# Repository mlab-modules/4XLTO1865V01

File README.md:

# 4XLTO1865V01 - LTO cells holder 

LTO cell holder for [SOLARMINIBAT01](https://github.com/mlab-modules/SOLARMINIBAT01) module.

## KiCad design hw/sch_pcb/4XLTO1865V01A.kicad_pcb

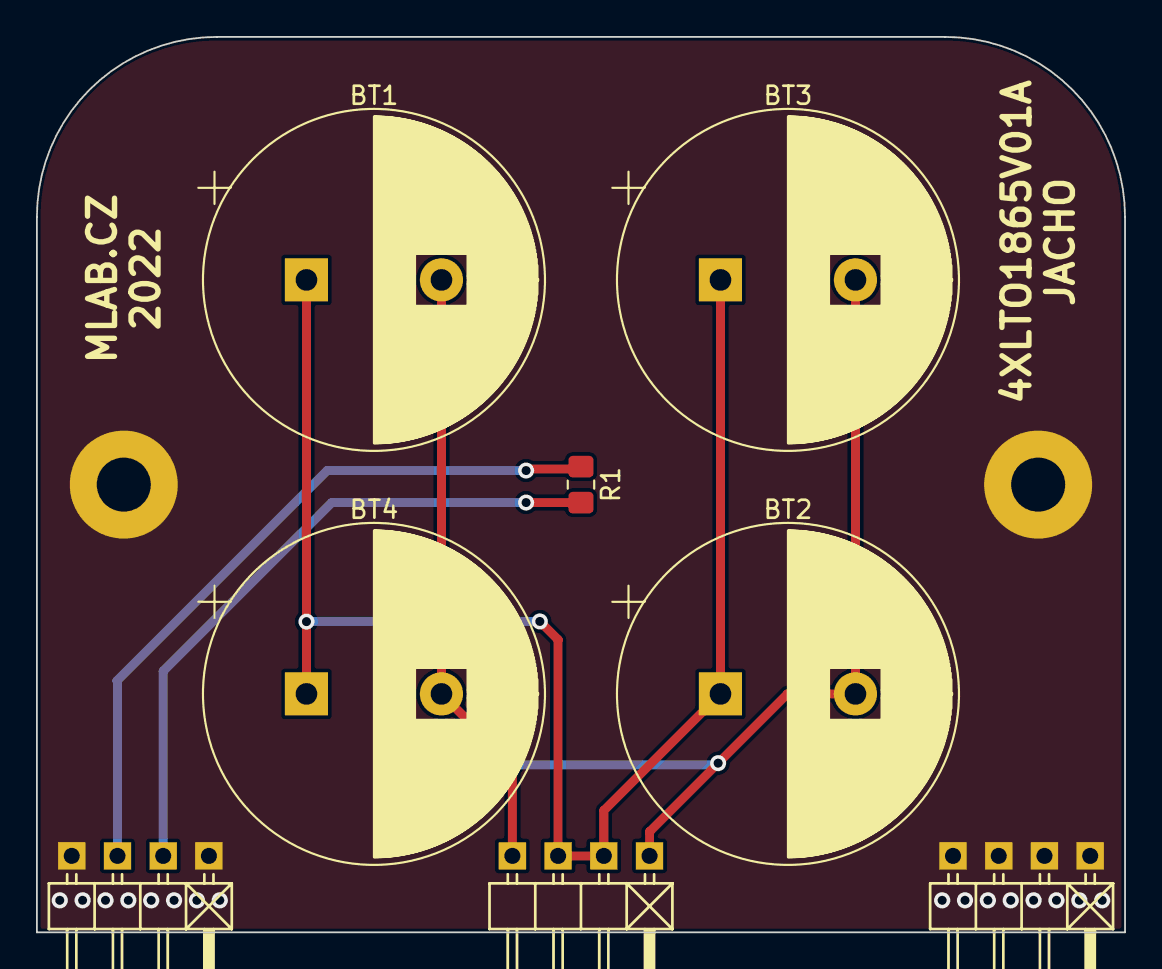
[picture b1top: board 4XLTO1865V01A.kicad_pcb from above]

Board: 2 copper layers, 60.5 x 49.7 mm, 10 parts (0 on the bottom side), 5 nets.

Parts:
BT1, BT2, BT3, BT4: LTO1865-13; LTO1865-13_D19.0mm_P7.50mm
J1, J2, J3: HEADER_2x04_PARALLEL; Angled_1x04
M1, M2: HOLE; MountingHole_3mm
R1: 10K NTC; R_0805_2012Metric_Pad1.20x1.40mm_HandSolder

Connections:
/Battery+: BT1.1 (+), BT2.1 (+), BT3.1 (+), BT4.1 (+), J1.2, J1.3
/Battery-: BT1.2 (-), BT2.2 (-), BT3.2 (-), BT4.2 (-), J1.1, J1.4
GND: J2.1, J2.4, J3.1, J3.2, J3.3, J3.4, M1.1, M2.1
unnamed: J2.2, R1.2
unnamed: J2.3, R1.1

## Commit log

2022-07-22 Edit schema and PCB
2022-07-22 Update actions products
2022-07-25 Edit PCB
2022-08-05 Edit
2023-09-17 automated commit; add github actions
2023-09-17 Update metadata files
2023-09-17 Update workflow files
